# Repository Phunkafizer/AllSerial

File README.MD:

# AllSerial
## An universal sophisticated USB-serial converter

SEE PROJECTHOMEPAGE UNDER [https://www.seegel-systeme.de/2025/07/10/allserial](https://www.seegel-systeme.de/2025/07/10/allserial)

Over the course of time I had to work with many different devices which had to be connected via a kind of serial interface. There are lots of different cheap USB-serial adapters available, but no adapter was including all features I needed in a single device. Every USB-serial adapter has in common the USB Controller. So I came up with the idea having a masterboard providing all the common features like USB interface, isolation and diagnostic elements. The most used interfaces (RS232, RS485, TTL UART, TTY current loop & LIN) are build up on slave modules which can be plugged into the mainboard. If a custom interface is needed, there is an KiCad library available making it easy to create one by yourself. 

## Features
- Open source
- Isolated
- Reset button for reenumerating device on the USB
- Status LEDs (RX, TX, Power, TXEN)
- modular, just exchange daughterboard for different interfaces
- RS232 completley connected (RXD, TXD, RTS, CTS, DTR, DSR, RI, DCD)
- RS485, RS422 with Handshake
- TTY current loop 4/3/2 wire active/passive
- LIN
- TTL 1.8/2.5/3.3/5 V
- KiCad library for easily creating custom modules

## Modules (tested & working)
* Mainboard FT232

* RS 422/485 

* RS 232 

* TTL 

* TTY current loop 

* LIN 

* 1wire (with DS2480B) 

* Programmer for ESP8266 (auto reset&boot) 

## Modules (under development)
* Mainboard with ESP32-S3 for accessing slave modules via USB, WiFi & Bluetooth 

* mBus master
* Digi XBee radiomodem 

* eBus 

## Software
* [hterm](http://www.der-hammer.info/terminal/) (windows)
* [putty](https://www.chiark.greenend.org.uk/~sgtatham/putty/latest.html) (windows/unix)

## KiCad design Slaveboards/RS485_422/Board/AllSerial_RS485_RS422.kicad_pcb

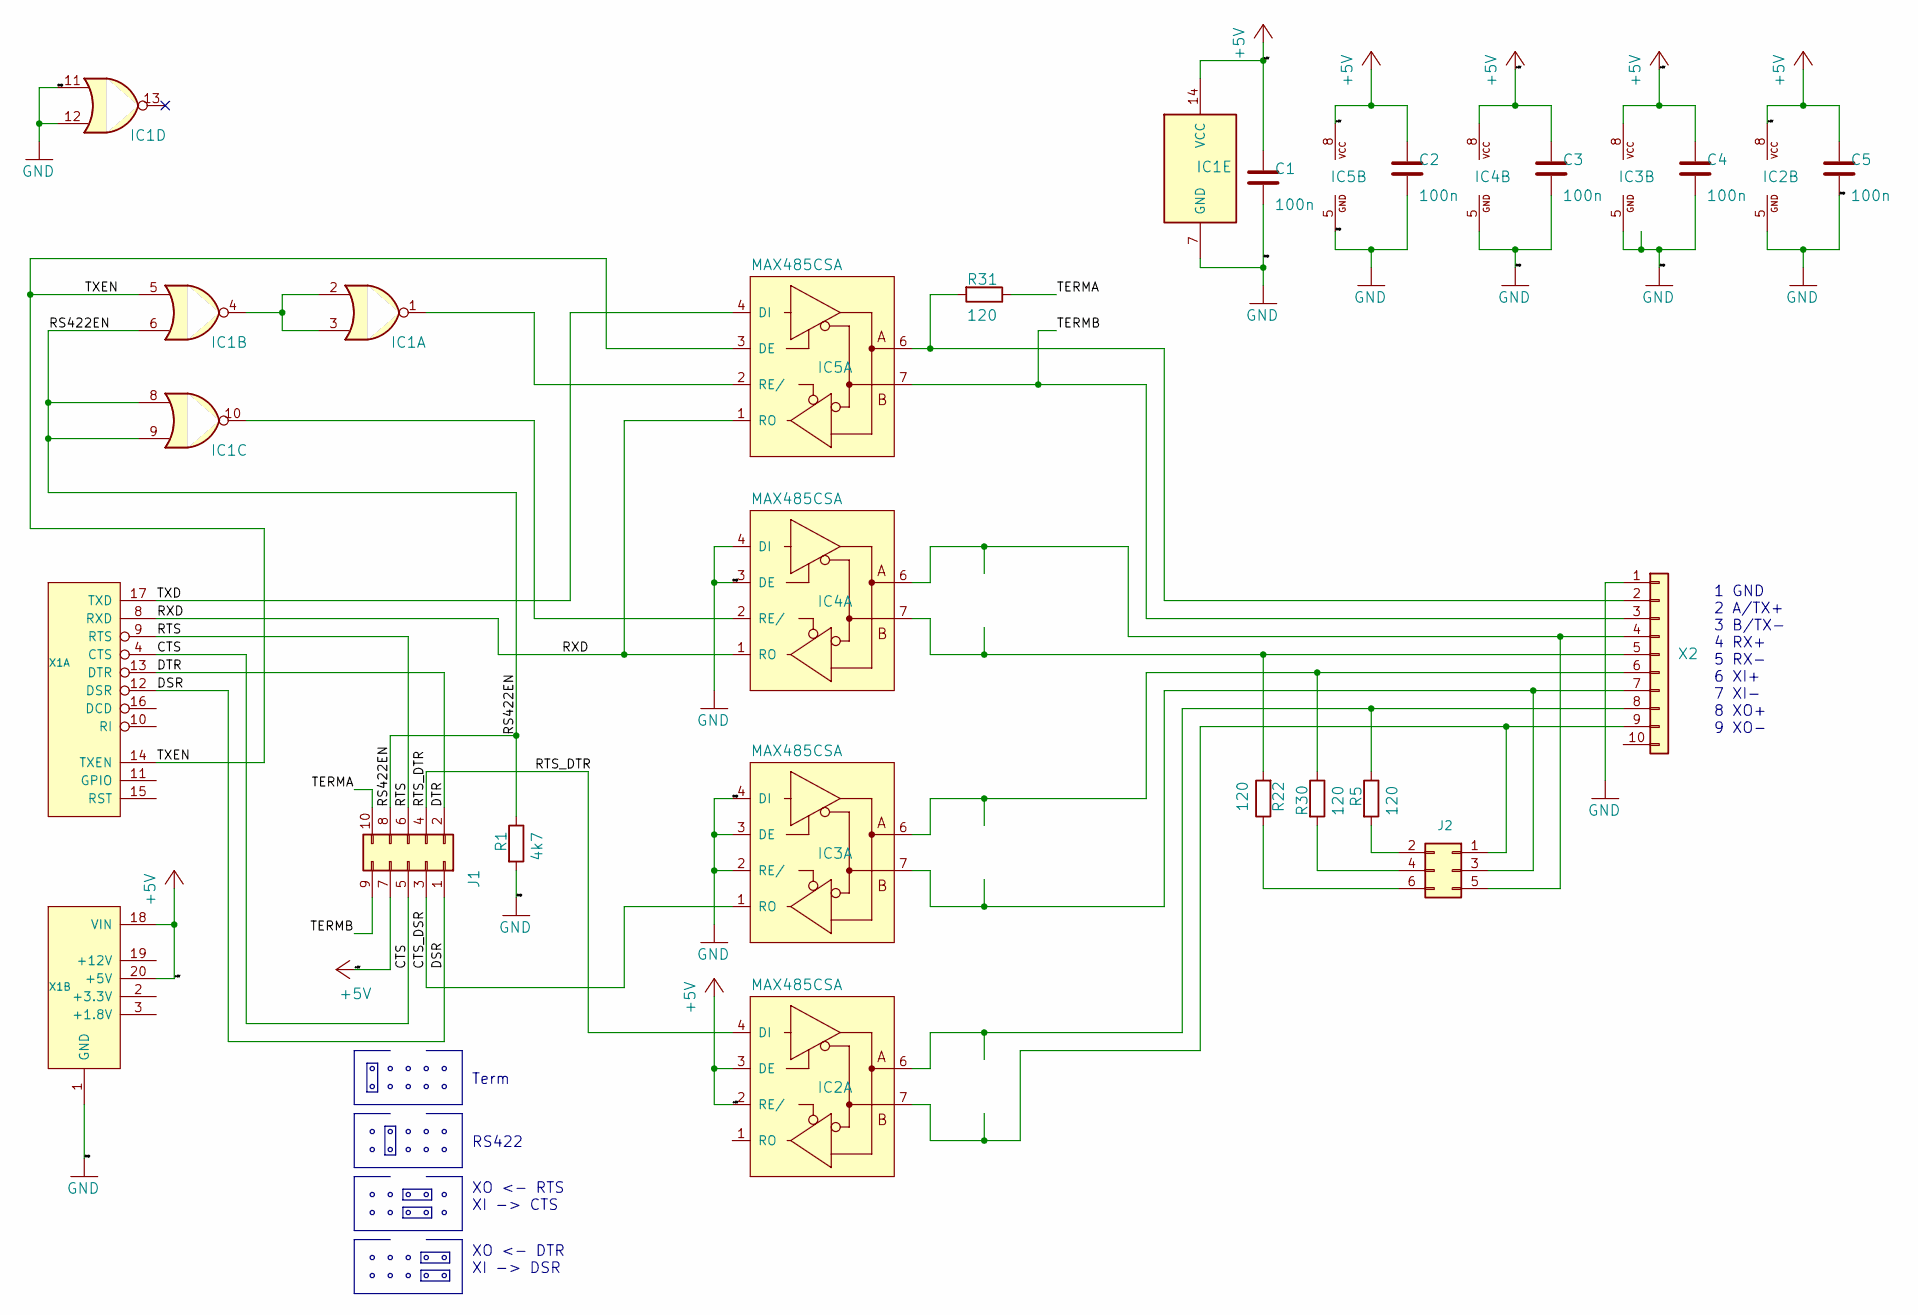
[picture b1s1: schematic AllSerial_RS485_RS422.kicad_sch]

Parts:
C1, C2, C3, C4, C5: 100n; C_0805_2012Metric
IC1: 7402D; SOIC-14_3.9x8.7mm_P1.27mm
IC2, IC3, IC4, IC5: MAX485CSA; SOIC-8_3.9x4.9mm_P1.27mm
J1: PinHeader_2x05_P2.54mm_Horizontal
J2: Conn_02x03_Odd_Even; PinHeader_2x03_P2.54mm_Vertical
R1: 4k7; R_0805_2012Metric
R5, R22, R30, R31: 120; R_0805_2012Metric
X1: ALLSERIALSLAVE; SlaveBoard
X2: AKL18X-10W; Metz_PT11310HBBN_182

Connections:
+5V: C1.1, C2.1, C3.1, C4.1, C5.1, IC1.14 (VCC), IC2.2 (RE/), IC2.3 (DE), IC2.8 (VCC), IC3.8 (VCC), IC4.8 (VCC), IC5.8 (VCC), J1.7, X1.18 (VIN), X1.20 (+5V)
/CTS: J1.5, X1.4 (CTS)
/CTS_DSR: IC3.1 (RO), J1.3
/DSR: J1.1, X1.12 (DSR)
/DTR: J1.2, X1.13 (DTR)
/RS422EN: IC1.6, IC1.8, IC1.9, J1.8, R1.1
/RTS: J1.6, X1.9 (RTS)
/RTS_DTR: IC2.4 (DI), J1.4
/RXD: IC4.1 (RO), IC5.1 (RO), X1.8 (RXD)
/TERMA: J1.10, R31.1
/TERMB: IC5.7 (B), J1.9, X2.3
/TXD: IC5.4 (DI), X1.17 (TXD)
/TXEN: IC1.5, IC5.3 (DE), X1.14 (TXEN)
GND: C1.2, C2.2, C3.2, C4.2, C5.2, IC1.7 (GND), IC1.11, IC1.12, IC2.5 (GND), IC3.2 (RE/), IC3.3 (DE), IC3.4 (DI), IC3.5 (GND), IC4.3 (DE), IC4.4 (DI), IC4.5 (GND), IC5.5 (GND), R1.2, X1.1 (GND), X2.1
unnamed: IC1.2, IC1.3, IC1.4
unnamed: IC2.6 (A), R5.1, X2.8
unnamed: IC2.7 (B), J2.1, X2.9
unnamed: IC3.6 (A), R30.1, X2.6
unnamed: IC3.7 (B), J2.3, X2.7
unnamed: IC4.6 (A), J2.5, X2.4
unnamed: IC4.7 (B), R22.2, X2.5
unnamed: IC1.10, IC4.2 (RE/)
unnamed: IC5.6 (A), R31.2, X2.2
unnamed: IC1.1, IC5.2 (RE/)
unnamed: J2.2, R5.2
unnamed: J2.4, R30.2
unnamed: J2.6, R22.1

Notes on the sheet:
1 GND 2 A/TX+ 3 B/TX- 4 RX+ 5 RX- 6 XI+ 7 XI- 8 XO+ 9 XO-
XO <- DTR XI -> DSR
RS422
Term
XO <- RTS XI -> CTS

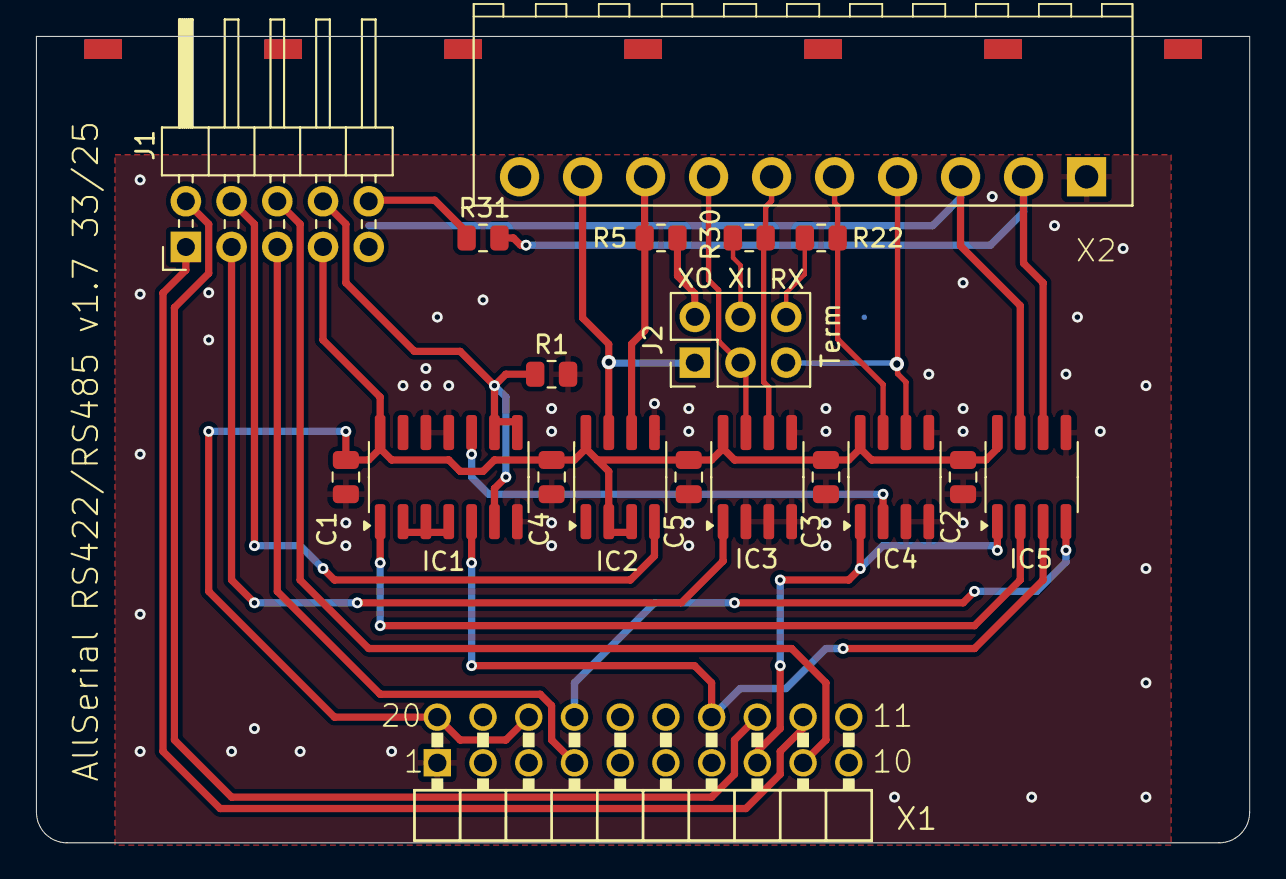
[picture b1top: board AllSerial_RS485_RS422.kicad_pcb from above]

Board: 2 copper layers, 67.4 x 44.8 mm, 19 parts (0 on the bottom side), 27 nets.

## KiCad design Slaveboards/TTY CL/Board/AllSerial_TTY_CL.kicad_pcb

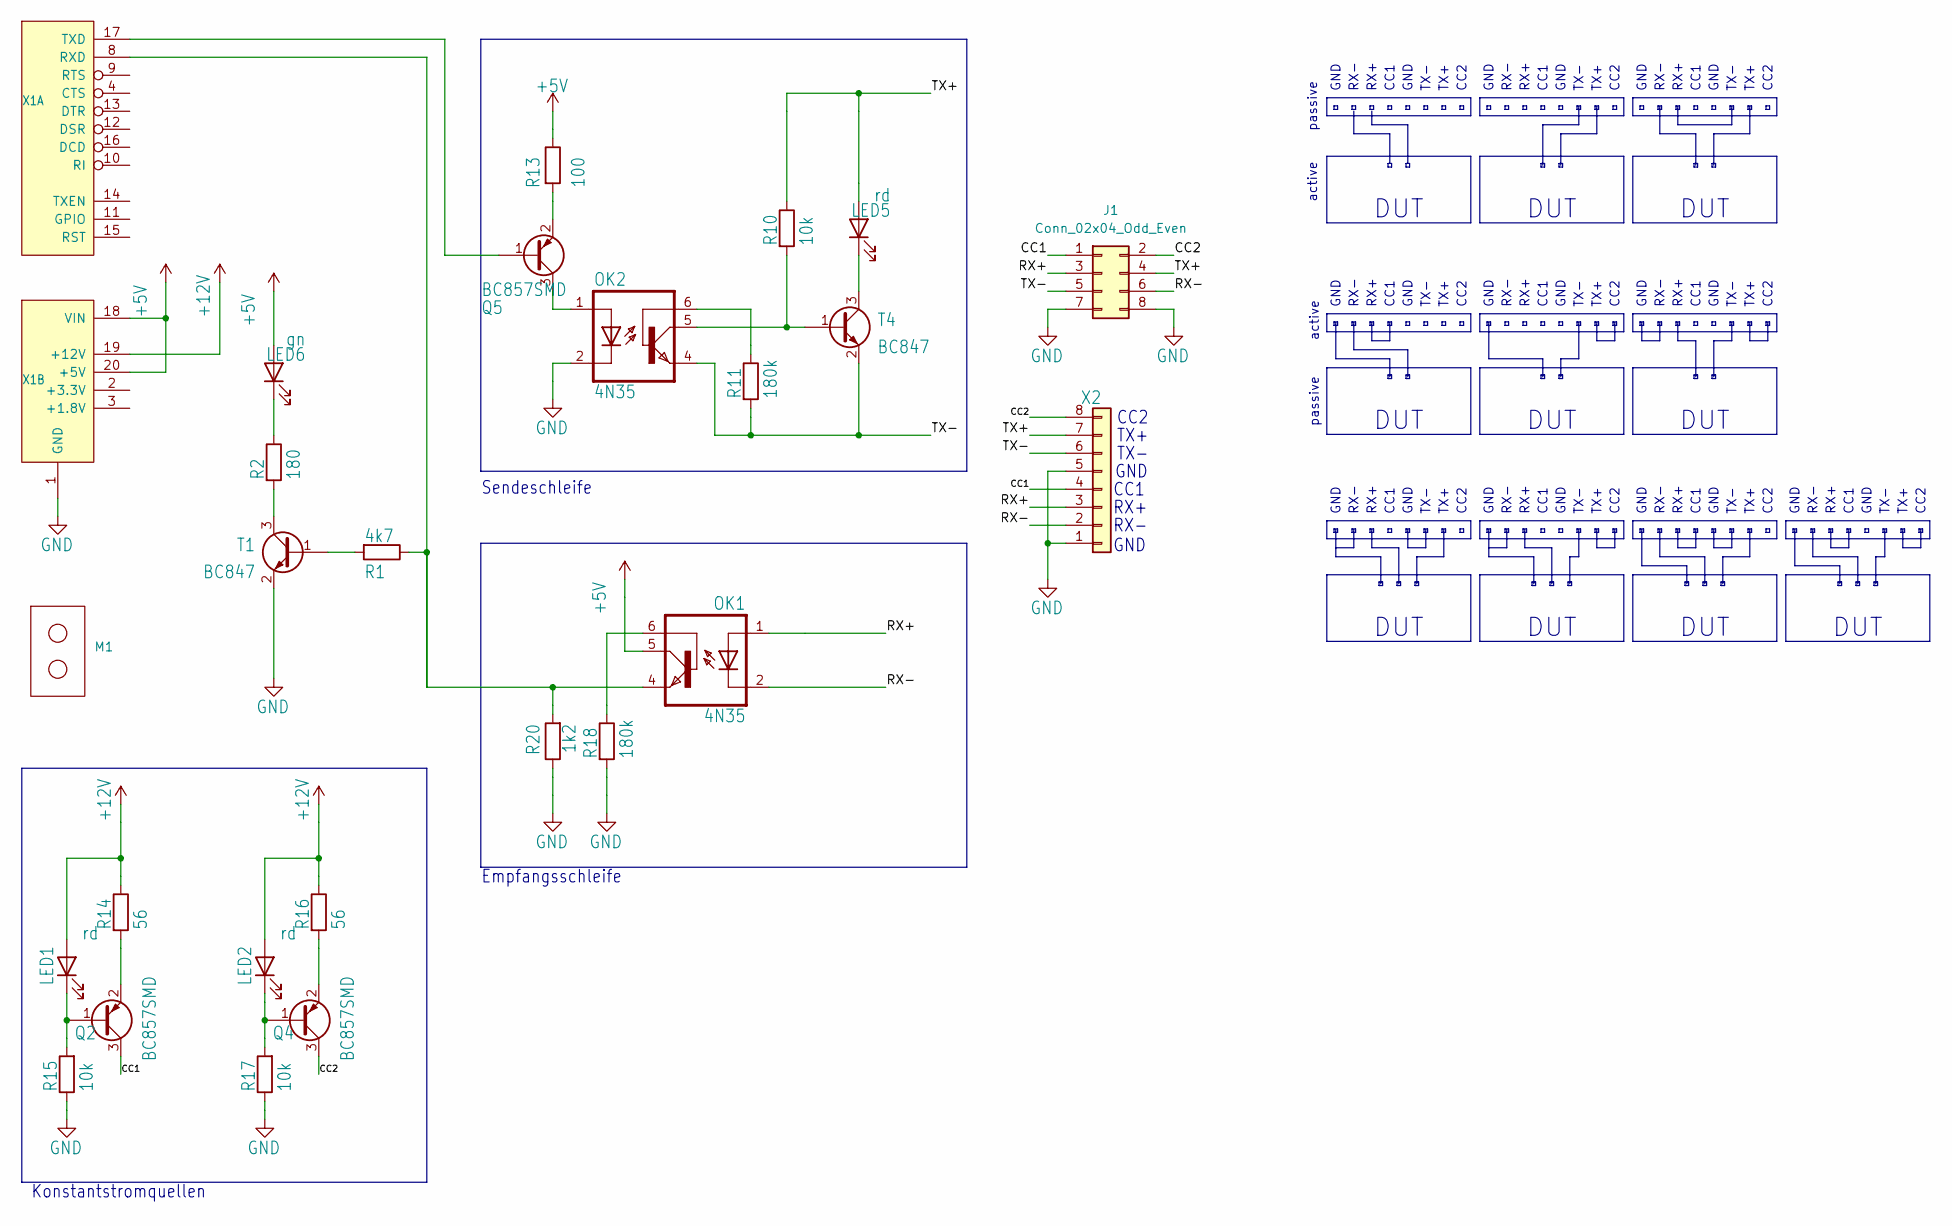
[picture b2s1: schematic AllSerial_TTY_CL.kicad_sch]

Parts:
J1: Conn_02x04_Odd_Even; PinHeader_2x04_P2.54mm_Horizontal
LED1, LED2, LED5: rd; LED_0603_1608Metric
LED6: gn; LED_0603_1608Metric
M1: Mentor 1296.2012
OK1, OK2: 4N35; DIL06; FARNELL 1612454
Q2, Q4, Q5: BC857SMD; SOT-23; FARNELL 8734771
R1: 4k7; R_0805_2012Metric; FARNELL 2498050
R2: 180; R_0805_2012Metric; FARNELL 2498090
R10: 10k; R_0805_2012Metric
R11, R18: 180k; R_0805_2012Metric; FARNELL 2498051
R13: 100; R_0805_2012Metric; FARNELL 2498057
R14, R16: 56; R_0805_2012Metric
R15, R17: 10k; R_0805_2012Metric; FARNELL 2502672
R20: 1k2; R_0805_2012Metric
T1, T4: BC847; SOT-23; FARNELL 1081230
X1: ALLSERIALSLAVE; SlaveBoard
X2: AKL18X-08W; Metz_PT11308HBBN_182

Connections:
+5V: LED6.2 (A), OK1.5 (COL), R13.1, X1.18 (VIN), X1.20 (+5V)
+12V: LED1.2 (A), LED2.2 (A), R14.1, R16.1, X1.19 (+12V)
/CC1: J1.1, Q2.3 (C), X2.4
/CC2: J1.2, Q4.3 (C), X2.8
/RX+: J1.3, OK1.1 (A), X2.3
/RX-: J1.6, OK1.2 (C), X2.2
/TX+: J1.4, LED5.2 (A), R10.1, X2.7
/TX-: J1.5, OK2.4 (EMI), R11.2, T4.2 (E), X2.6
GND: J1.7, J1.8, OK2.2 (C), R15.1, R17.1, R18.2, R20.1, T1.2 (E), X1.1 (GND), X2.1, X2.5
unnamed: LED1.1 (K), Q2.1 (B), R15.2
unnamed: LED2.1 (K), Q4.1 (B), R17.2
unnamed: LED5.1 (K), T4.3 (C)
unnamed: LED6.1 (K), R2.1
unnamed: OK1.6 (BAS), R18.1
unnamed: OK1.4 (EMI), R1.1, R20.2, X1.8 (RXD)
unnamed: OK2.1 (A), Q5.3 (C)
unnamed: OK2.6 (BAS), R11.1
unnamed: OK2.5 (COL), R10.2, T4.1 (B)
unnamed: Q2.2 (E), R14.2
unnamed: Q4.2 (E), R16.2
unnamed: Q5.1 (B), X1.17 (TXD)
unnamed: Q5.2 (E), R13.2
unnamed: R1.2, T1.1 (B)
unnamed: R2.2, T1.3 (C)

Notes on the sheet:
RX+
DUT
GND
CC2
active
CC1
TX-
TX+
RX-
passive
Konstantstromquellen
Sendeschleife
Empfangsschleife

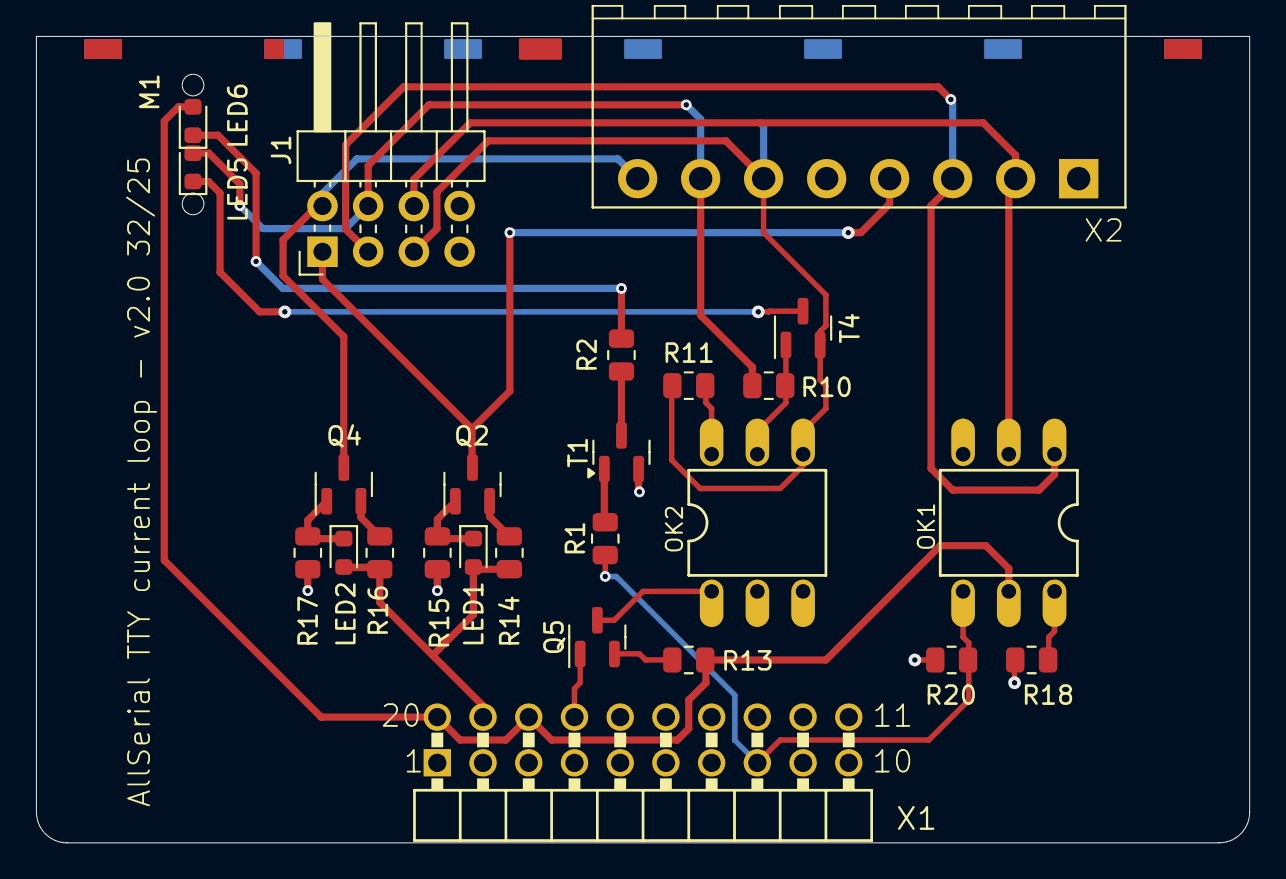
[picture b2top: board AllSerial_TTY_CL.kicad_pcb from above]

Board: 2 copper layers, 67.4 x 44.8 mm, 26 parts (0 on the bottom side), 24 nets.

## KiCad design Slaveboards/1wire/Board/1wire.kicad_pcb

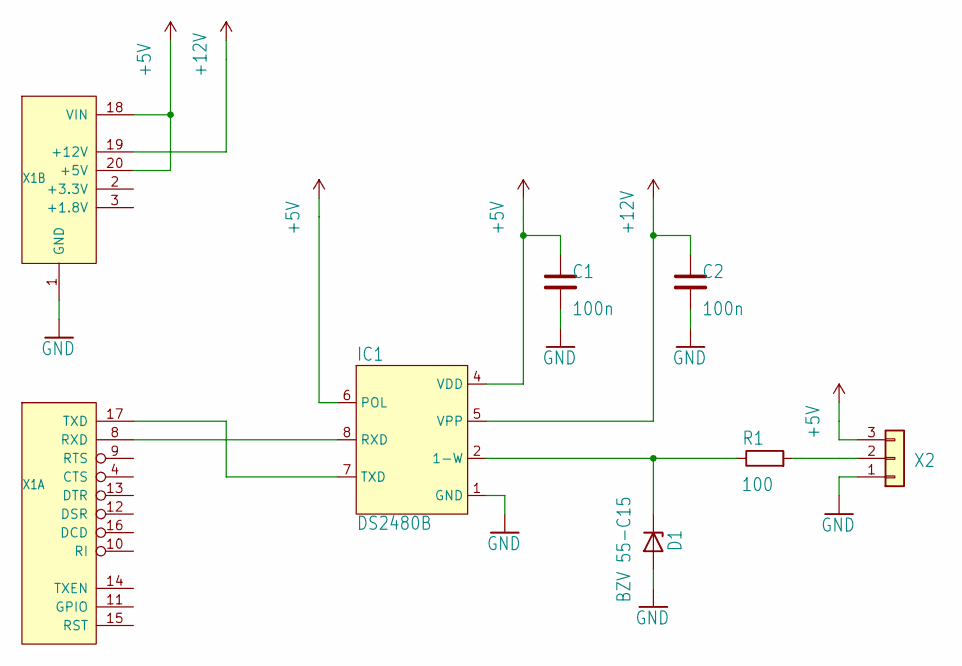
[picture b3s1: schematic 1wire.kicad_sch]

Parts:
C1, C2: 100n; C_0805_2012Metric
D1: BZV 55-C15; D_MiniMELF
IC1: DS2480B; SOIC-8_3.9x4.9mm_P1.27mm
R1: 100; R_0805_2012Metric
X1: ALLSERIALSLAVE; SlaveBoard
X2: AKL18X-03W; Metz_PT11303HBBN_182

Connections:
+5V: C1.1, IC1.4 (VDD), IC1.6 (POL), X1.18 (VIN), X1.20 (+5V), X2.3
+12V: C2.1, IC1.5 (VPP), X1.19 (+12V)
GND: C1.2, C2.2, D1.2 (A), IC1.1 (GND), X1.1 (GND), X2.1
unnamed: D1.1 (K), IC1.2 (1-W), R1.1
unnamed: IC1.8 (RXD), X1.8 (RXD)
unnamed: IC1.7 (TXD), X1.17 (TXD)
unnamed: R1.2, X2.2

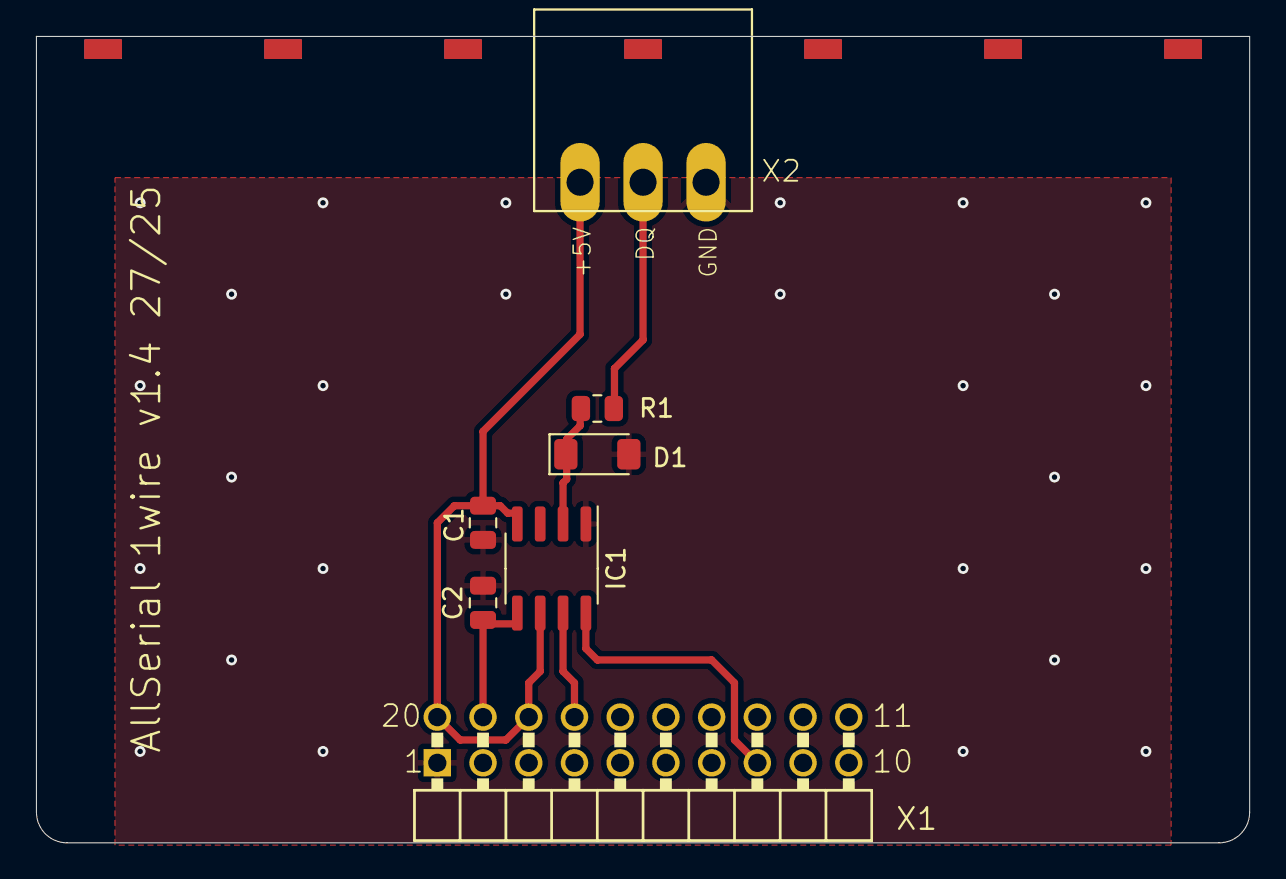
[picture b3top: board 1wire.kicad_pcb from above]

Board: 2 copper layers, 67.4 x 44.8 mm, 7 parts (0 on the bottom side), 7 nets.

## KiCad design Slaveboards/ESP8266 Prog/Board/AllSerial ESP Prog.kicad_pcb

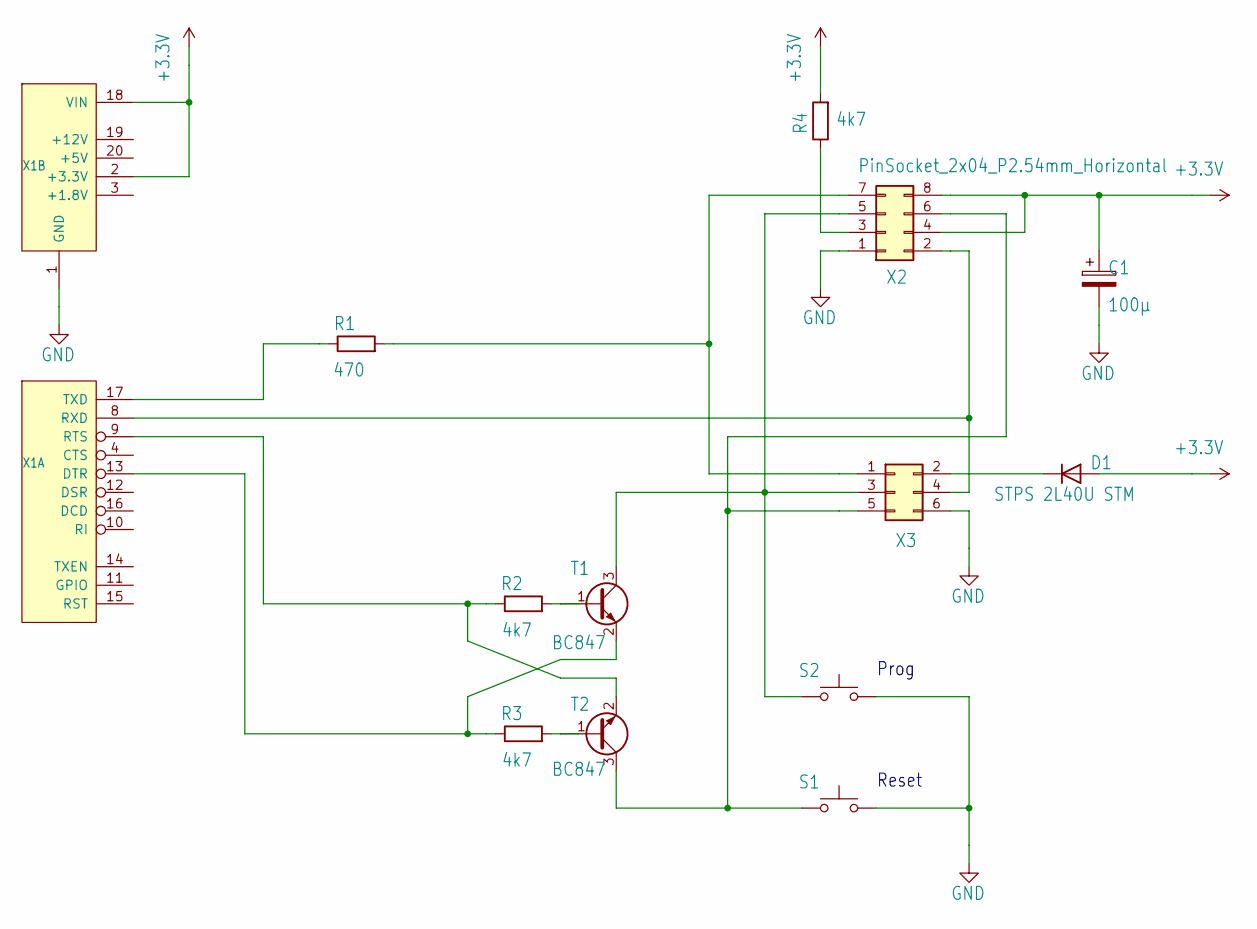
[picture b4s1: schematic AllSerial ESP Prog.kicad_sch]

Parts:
C1: 100µ; CP_Elec_6.3x5.4
D1: STPS 2L40U STM; D_SMB
R1: 470; R_0805_2012Metric
R2, R3, R4: 4k7; R_0805_2012Metric
S1, S2: SW_Tactile_SPST_Angled_PTS645Vx83-2LFS
T1, T2: BC847; SOT-23
X1: ALLSERIALSLAVE; SlaveBoard
X2: PinSocket_2x04_P2.54mm_Horizontal
X3: IDC-Header_2x03_P2.54mm_Horizontal

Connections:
+3.3V: C1.1, D1.2 (A), R4.2, X1.2 (+3.3V), X1.18 (VIN), X2.4, X2.8
GND: C1.2, S1.1, S2.1, X1.1 (GND), X2.1, X3.6
unnamed: D1.1 (K), X3.2
unnamed: R2.2, T1.1 (B)
unnamed: S2.2, T1.3 (C), X2.5, X3.3
unnamed: R3.1, T1.2 (E), X1.13 (DTR)
unnamed: R3.2, T2.1 (B)
unnamed: S1.2, T2.3 (C), X2.6, X3.5
unnamed: R2.1, T2.2 (E), X1.9 (RTS)
unnamed: X1.8 (RXD), X2.2, X3.4
unnamed: R1.1, X1.17 (TXD)
unnamed: R4.1, X2.3
unnamed: R1.2, X2.7, X3.1

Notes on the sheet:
Reset
Prog

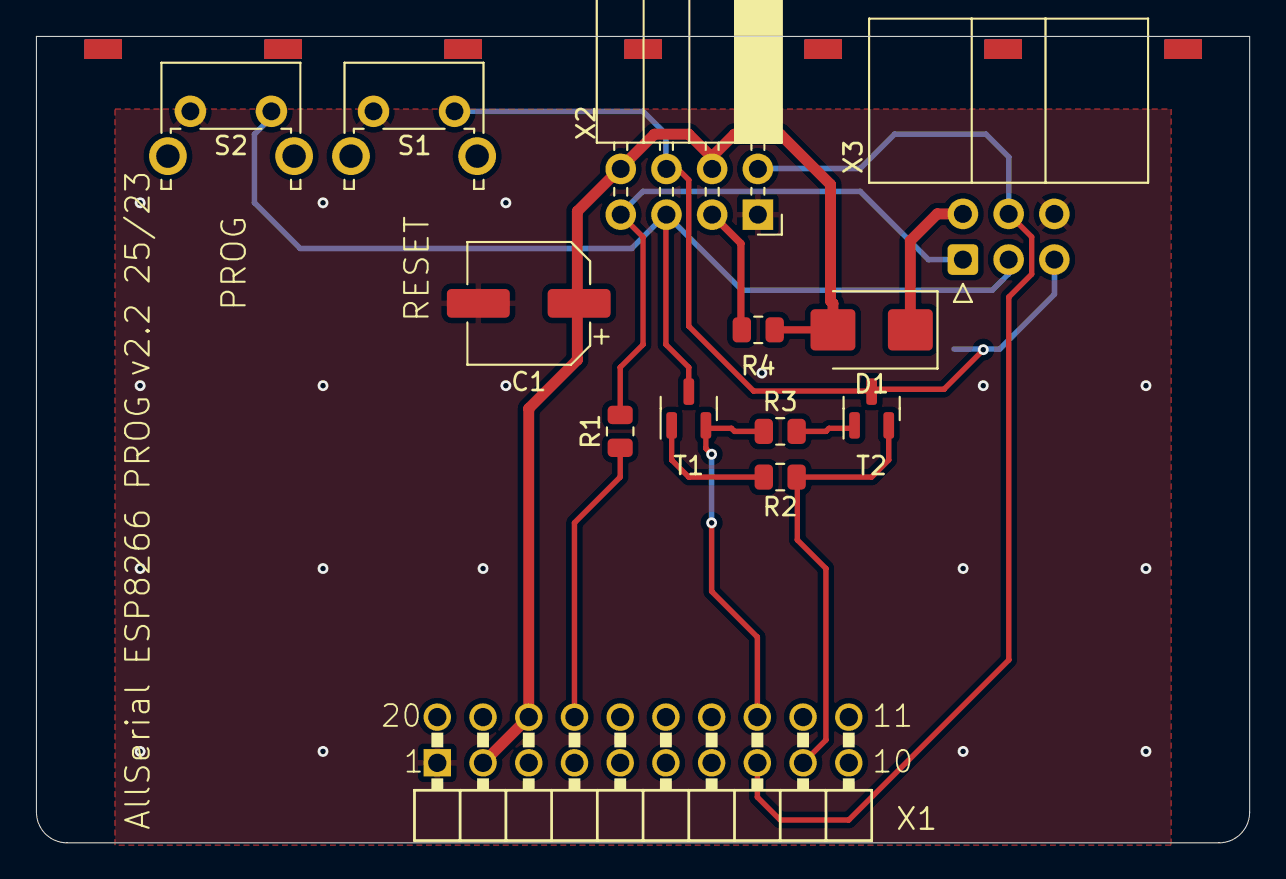
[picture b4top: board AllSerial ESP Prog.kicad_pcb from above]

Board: 2 copper layers, 67.4 x 44.8 mm, 13 parts (0 on the bottom side), 13 nets.

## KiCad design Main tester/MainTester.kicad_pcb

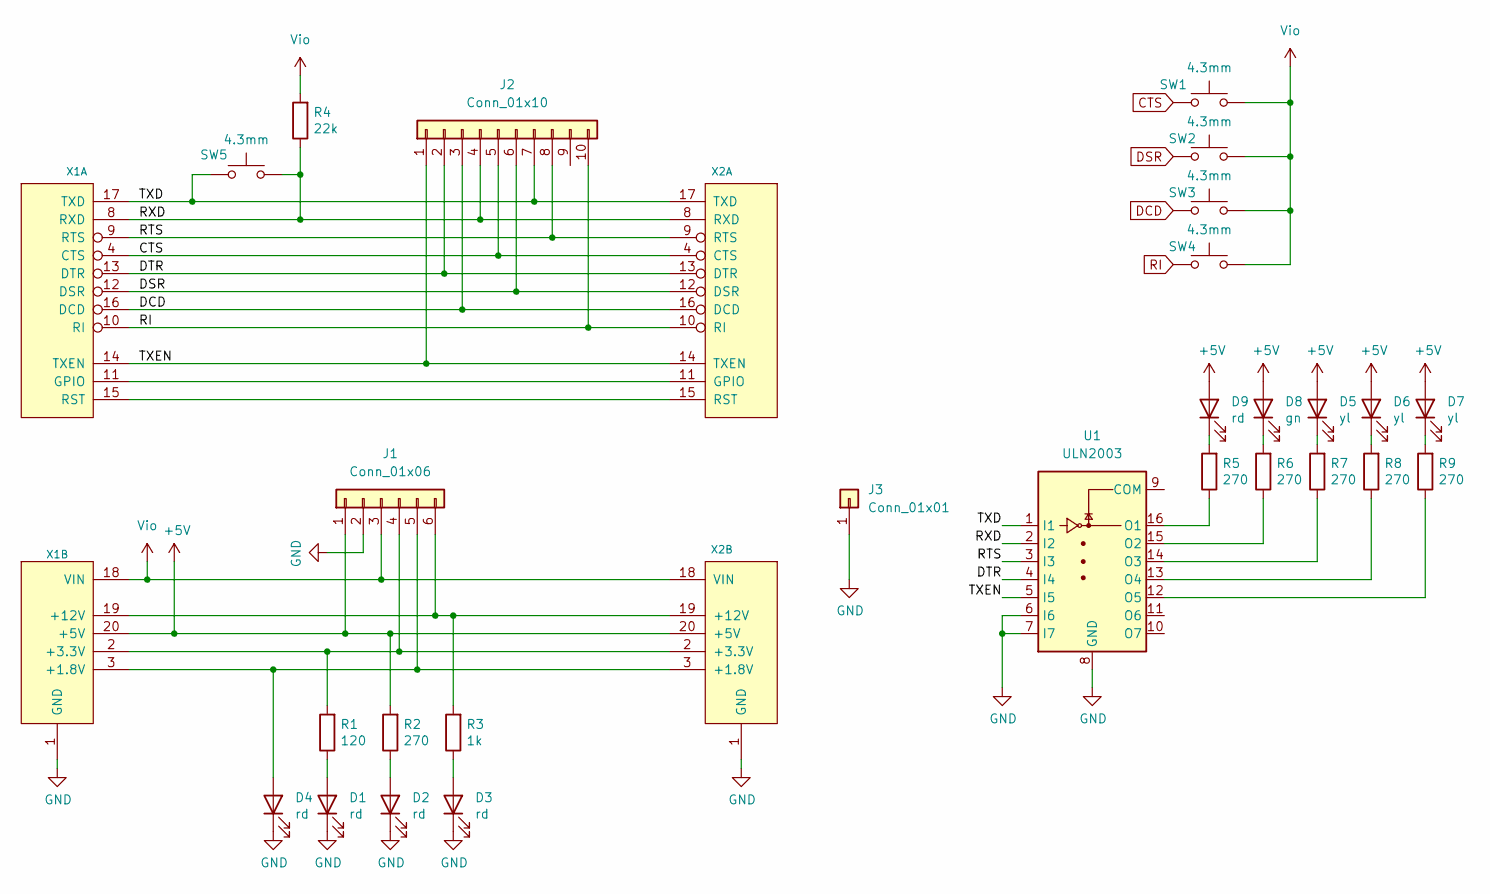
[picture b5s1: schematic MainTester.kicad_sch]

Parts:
D1, D2, D3, D4, D9: rd; LED_0805_2012Metric
D5, D6, D7: yl; LED_0805_2012Metric
D8: gn; LED_0805_2012Metric
J1: Conn_01x06; PinHeader_2x03_P2.54mm_Vertical
J2: Conn_01x10; PinHeader_2x05_P2.54mm_Vertical
J3: Conn_01x01; PinHeader_1x01_P2.54mm_Vertical
R1: 120; R_0805_2012Metric
R2, R5, R6, R7, R8, R9: 270; R_0805_2012Metric
R3: 1k; R_0805_2012Metric
R4: 22k; R_0805_2012Metric
SW1, SW2, SW3, SW4, SW5: 4.3mm; SW_SPST_PTS645
U1: ULN2003; SO-16_3.9x9.9mm_P1.27mm
X1: ALLSERIALSLAVE; SlaveBoard
X2: ALLSERIALSLAVE; Master PinSocket

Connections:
+5V: D5.2 (A), D6.2 (A), D7.2 (A), D8.2 (A), D9.2 (A), J1.1, R2.2, X1.20 (+5V), X2.20 (+5V)
/DTR: J2.2, U1.4 (I4), X1.13 (DTR), X2.13 (DTR)
/RTS: J2.8, U1.3 (I3), X1.9 (RTS), X2.9 (RTS)
/RXD: J2.4, R4.1, SW5.1, U1.2 (I2), X1.8 (RXD), X2.8 (RXD)
/TXD: J2.7, SW5.2, U1.1 (I1), X1.17 (TXD), X2.17 (TXD)
/TXEN: J2.1, U1.5 (I5), X1.14 (TXEN), X2.14 (TXEN)
CTS: J2.5, SW1.1, X1.4 (CTS), X2.4 (CTS)
DCD: J2.3, SW3.1, X1.16 (DCD), X2.16 (DCD)
DSR: J2.6, SW2.1, X1.12 (DSR), X2.12 (DSR)
GND: D1.1 (K), D2.1 (K), D3.1 (K), D4.1 (K), J1.2, J3.1, U1.6 (I6), U1.7 (I7), U1.8 (GND), X1.1 (GND), X2.1 (GND)
unnamed: D1.2 (A), R1.1
unnamed: D2.2 (A), R2.1
unnamed: D3.2 (A), R3.1
unnamed: D4.2 (A), J1.5, X1.3 (+1.8V), X2.3 (+1.8V)
unnamed: D5.1 (K), R7.2
unnamed: D6.1 (K), R8.2
unnamed: D7.1 (K), R9.2
unnamed: D8.1 (K), R6.2
unnamed: D9.1 (K), R5.2
unnamed: J1.4, R1.2, X1.2 (+3.3V), X2.2 (+3.3V)
unnamed: J1.6, R3.2, X1.19 (+12V), X2.19 (+12V)
unnamed: R5.1, U1.16 (O1)
unnamed: R6.1, U1.15 (O2)
unnamed: R7.1, U1.14 (O3)
unnamed: R8.1, U1.13 (O4)
unnamed: R9.1, U1.12 (O5)
unnamed: X1.11 (GPIO), X2.11 (GPIO)
unnamed: X1.15 (RST), X2.15 (RST)
RI: J2.10, SW4.1, X1.10 (RI), X2.10 (RI)
Vio: J1.3, R4.2, SW1.2, SW2.2, SW3.2, SW4.2, X1.18 (VIN), X2.18 (VIN)

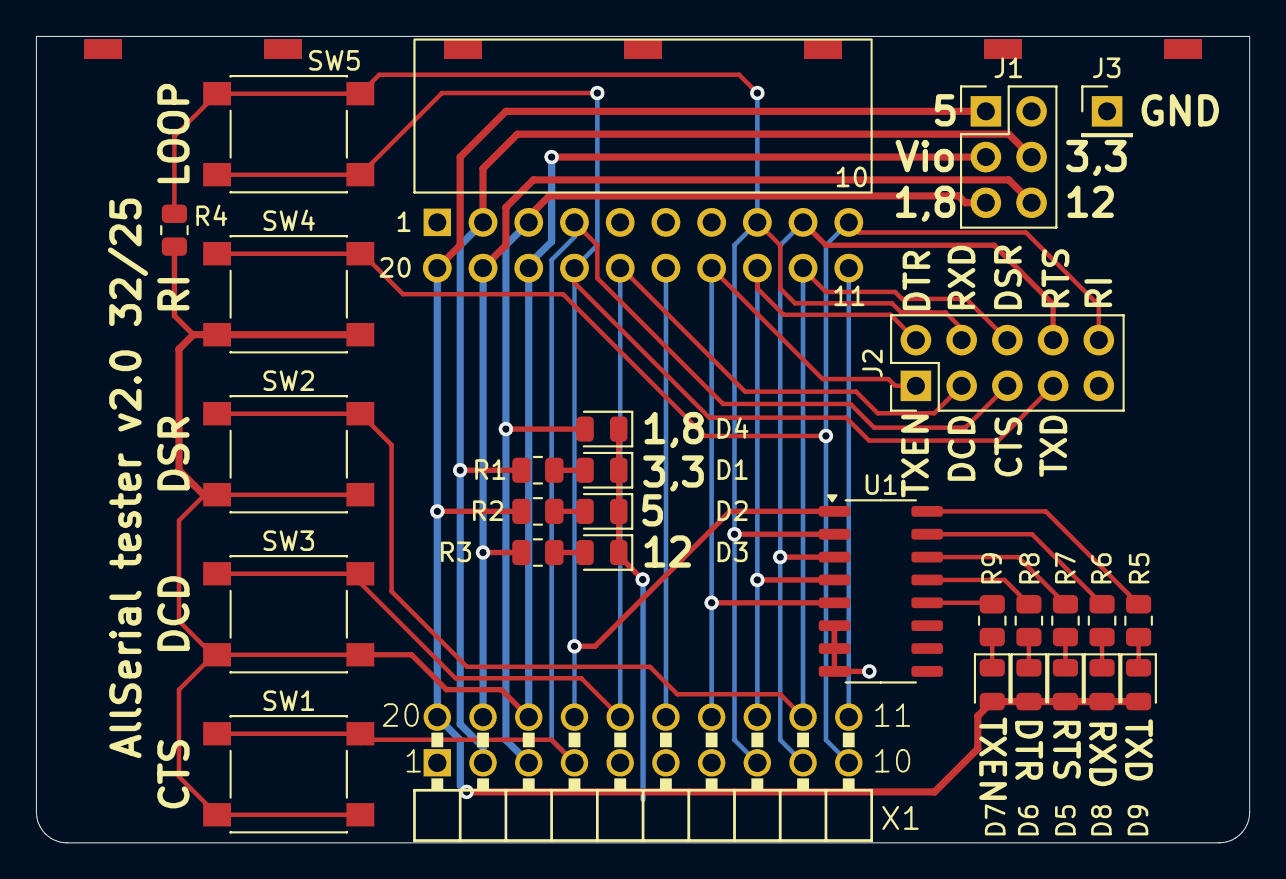
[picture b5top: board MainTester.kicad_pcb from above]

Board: 2 copper layers, 67.4 x 44.8 mm, 29 parts (0 on the bottom side), 30 nets.

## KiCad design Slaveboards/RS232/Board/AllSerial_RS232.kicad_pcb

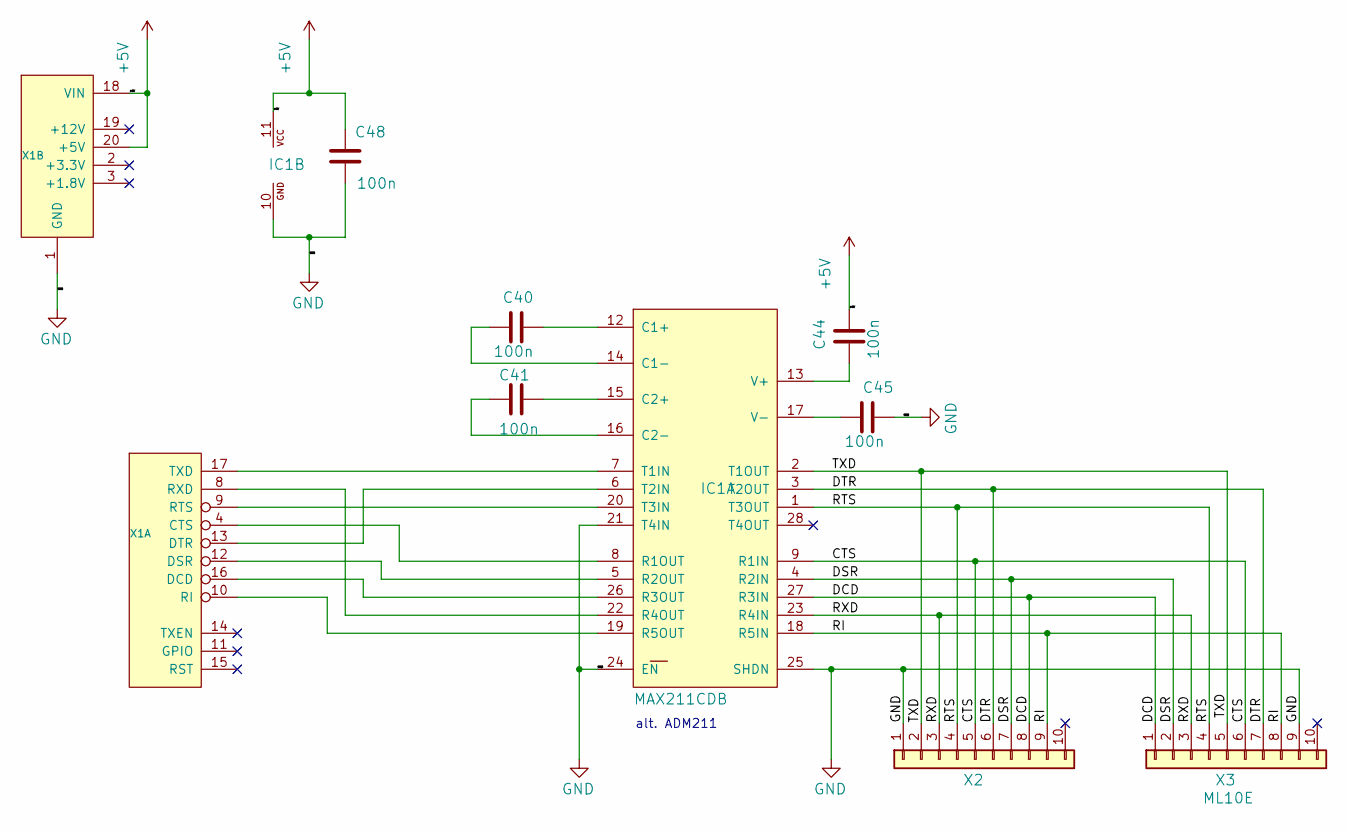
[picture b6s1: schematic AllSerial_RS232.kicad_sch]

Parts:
C40, C41, C44, C45, C48: 100n; C_0805_2012Metric
IC1: MAX211CDB; SSOP-28_5.3x10.2mm_P0.65mm
X1: ALLSERIALSLAVE; SlaveBoard
X2: AKL18X-10W; Metz_PT11310HBBN_182
X3: ML10E; IDC-Header_2x05_P2.54mm_Vertical

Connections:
+5V: C44.2, C48.1, IC1.11 (VCC), X1.18 (VIN), X1.20 (+5V)
/CTS: IC1.9 (R1IN), X2.5, X3.6
/DCD: IC1.27 (R3IN), X2.8, X3.1
/DSR: IC1.4 (R2IN), X2.7, X3.2
/DTR: IC1.3 (T2OUT), X2.6, X3.7
/RI: IC1.18 (R5IN), X2.9, X3.8
/RTS: IC1.1 (T3OUT), X2.4, X3.4
/RXD: IC1.23 (R4IN), X2.3, X3.3
/TXD: IC1.2 (T1OUT), X2.2, X3.5
GND: C45.2, C48.2, IC1.10 (GND), IC1.21 (T4IN), IC1.24 (EN), IC1.25 (SHDN), X1.1 (GND), X2.1, X3.9
unnamed: C40.2, IC1.12 (C1+)
unnamed: C40.1, IC1.14 (C1-)
unnamed: C41.1, IC1.15 (C2+)
unnamed: C41.2, IC1.16 (C2-)
unnamed: IC1.8 (R1OUT), X1.4 (CTS)
unnamed: IC1.5 (R2OUT), X1.12 (DSR)
unnamed: IC1.26 (R3OUT), X1.16 (DCD)
unnamed: IC1.22 (R4OUT), X1.8 (RXD)
unnamed: IC1.19 (R5OUT), X1.10 (RI)
unnamed: IC1.7 (T1IN), X1.17 (TXD)
unnamed: IC1.6 (T2IN), X1.13 (DTR)
unnamed: IC1.20 (T3IN), X1.9 (RTS)
unnamed: C44.1, IC1.13 (V+)
unnamed: C45.1, IC1.17 (V-)

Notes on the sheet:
alt. ADM211

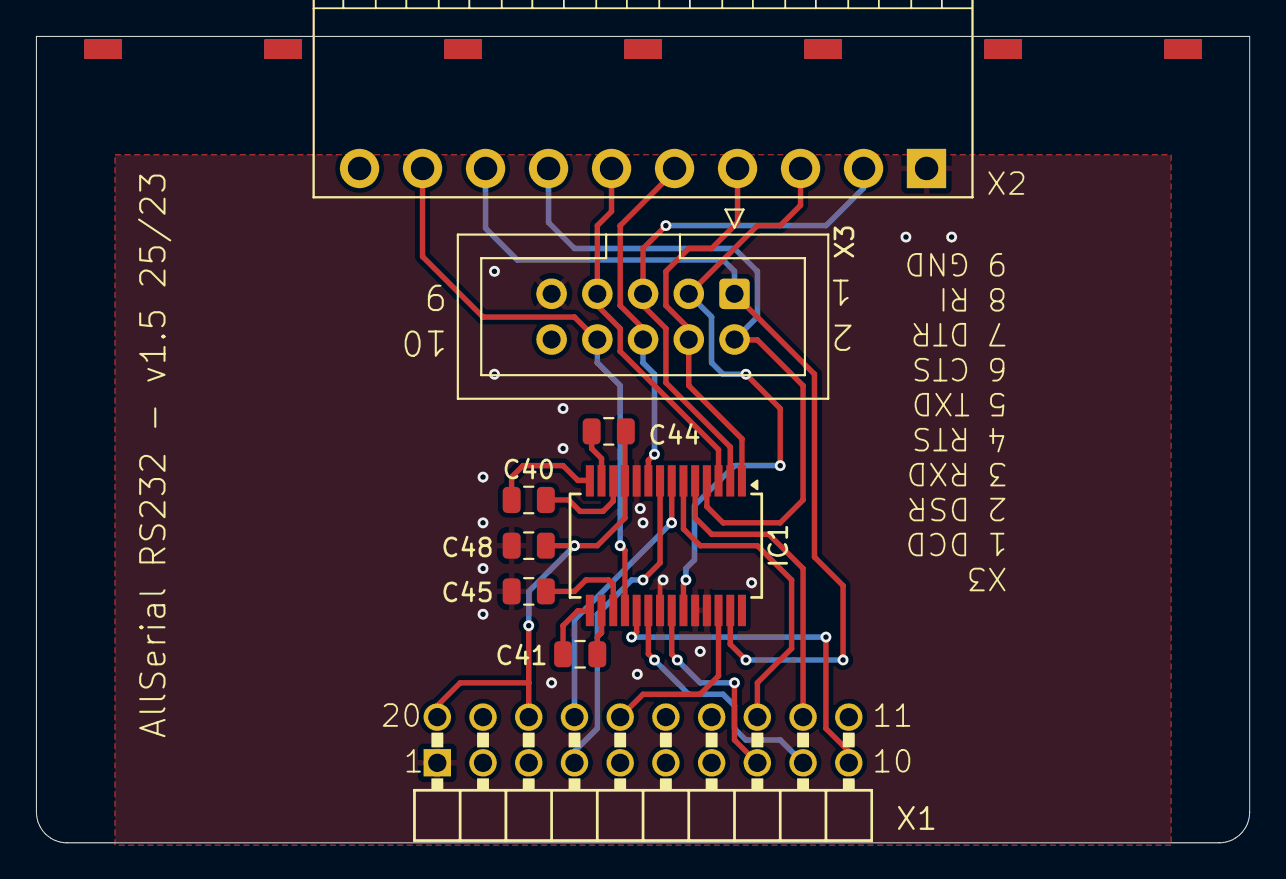
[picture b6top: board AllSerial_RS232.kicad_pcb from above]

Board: 2 copper layers, 67.4 x 44.8 mm, 9 parts (0 on the bottom side), 24 nets.
